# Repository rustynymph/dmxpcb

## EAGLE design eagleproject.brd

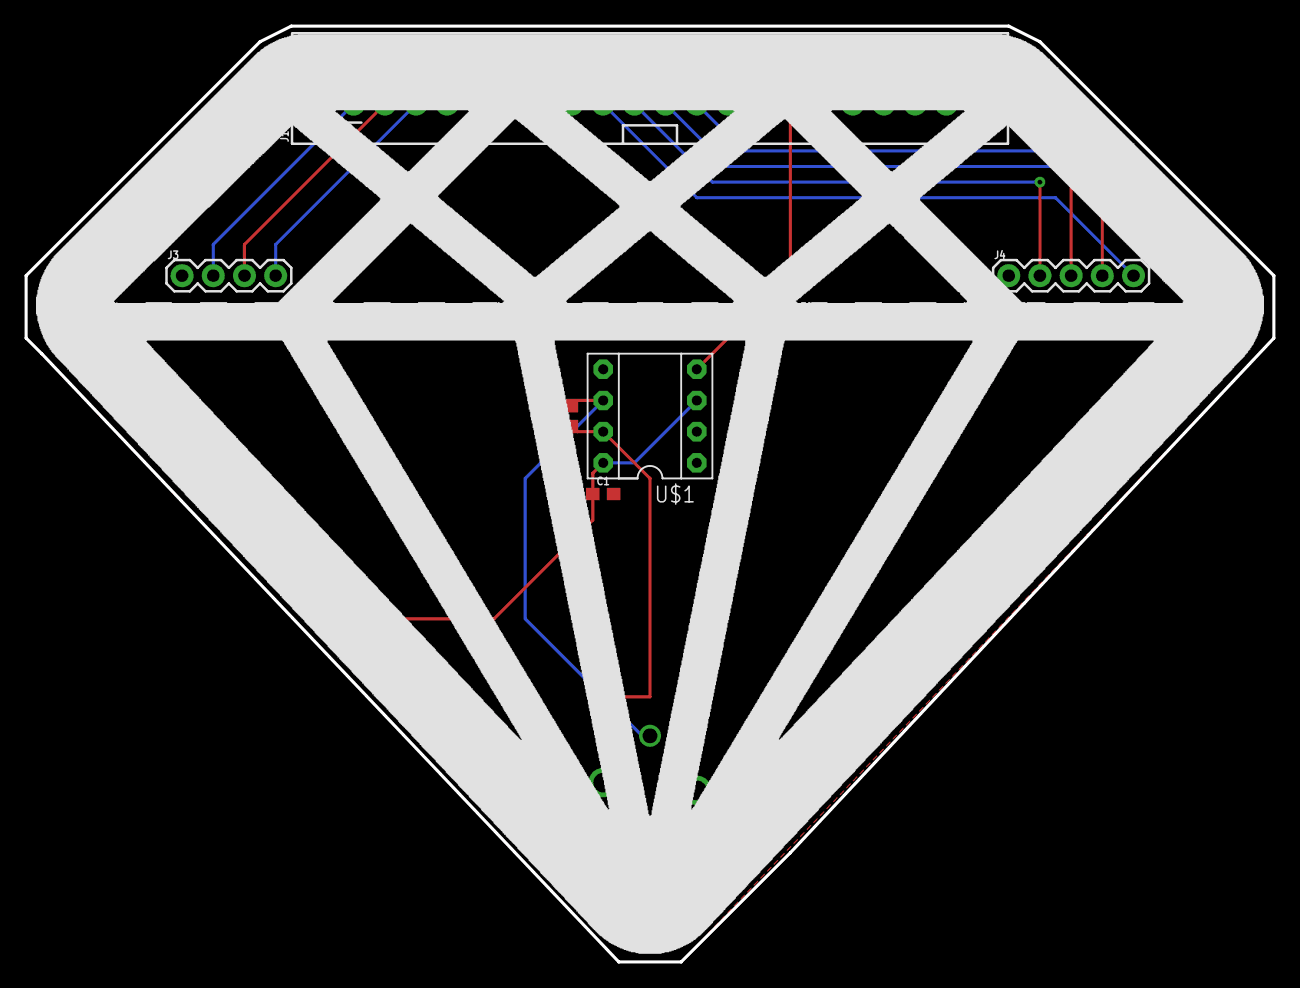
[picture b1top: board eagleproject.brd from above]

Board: 2 copper layers, 101.6 x 76.2 mm, 9 parts (1 on the bottom side), 11 nets.

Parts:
C1: 0.1uF; 0603
J1: RASPBERRYPI-40-PIN-GPIO_PTH; 2X20_SHROUDED
J2: XLR-3-FEMALE; XLR-3_FEMALE
J3: 1X04
J4: 1X05
R1: 100; 0603
U$1: MAX485DIL; DIL08
U$2: DIAMONDIMAGE#JPEG
U$3: NAMEFORPCB#JPG

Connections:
3.3V: J1.1, J1.17, J3.2, J4.5
5V: C1.1, J1.2, J1.4, U$1.3, U$1.8
A: J2.3, R1.2, U$1.6
B: J2.2, R1.1, U$1.7
DI: J1.29, U$1.4
GND: C1.2, J1.6, J1.9, J1.14, J1.20, J1.25, J1.30, J1.34, J1.39, J2.1, J3.1, J4.1, U$1.1, U$1.2, U$1.5
MISO: J1.21, J4.3
MOSI: J1.19, J4.2
SCL: J1.5, J3.4
SCLK: J1.23, J4.4
SDA: J1.3, J3.3

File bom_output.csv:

Qty, PROD_ID, Names, Value, Package
1, CAP-00810, C1, 0.1uF, 0603
1, CONN-12263, J1, RASPBERRYPI-40-PIN-GPIO_PTH, 2X20_SHROUDED
1, CONN-14142, J2, XLR-3-FEMALE, XLR-3_FEMALE
1, RES-12438, R1, 100, 0603

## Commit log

2019-12-04 documentation for velleman part
2019-12-04 sparkfun libraries i didn't have
2019-12-04 velleman user manual
2019-12-05 first version for manufacturing
2019-12-05 reorganized files into subfolders

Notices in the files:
parts and their libraries:
SparkFun-Connectors: Licensing: Creative Commons ShareAlike 4.0 International - https://creativecommons.org/licenses/by-sa/4.0
